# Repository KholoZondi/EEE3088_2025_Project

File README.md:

The repo stores all the shared work between EEE3088F Group 58 members Kholofelo Zondi and Max Mendelow for the Micro-mouse project project 2025. 

This includes the datasheets for certain ICs, past designs, general personal notes, downloaded schematics and the final design with Gerber and production files.

For the final design of the power subsystem, please navigate to "Micro_mouse_circuit/Micro_mouse_final" and consider the contents of the folder "Micro_mouse final" 
as the final design as of April 9th 2025. 

Full names and student numbers
Kholofelo Zondi ZNDKHO003
Max Mendelow MNDMAX003

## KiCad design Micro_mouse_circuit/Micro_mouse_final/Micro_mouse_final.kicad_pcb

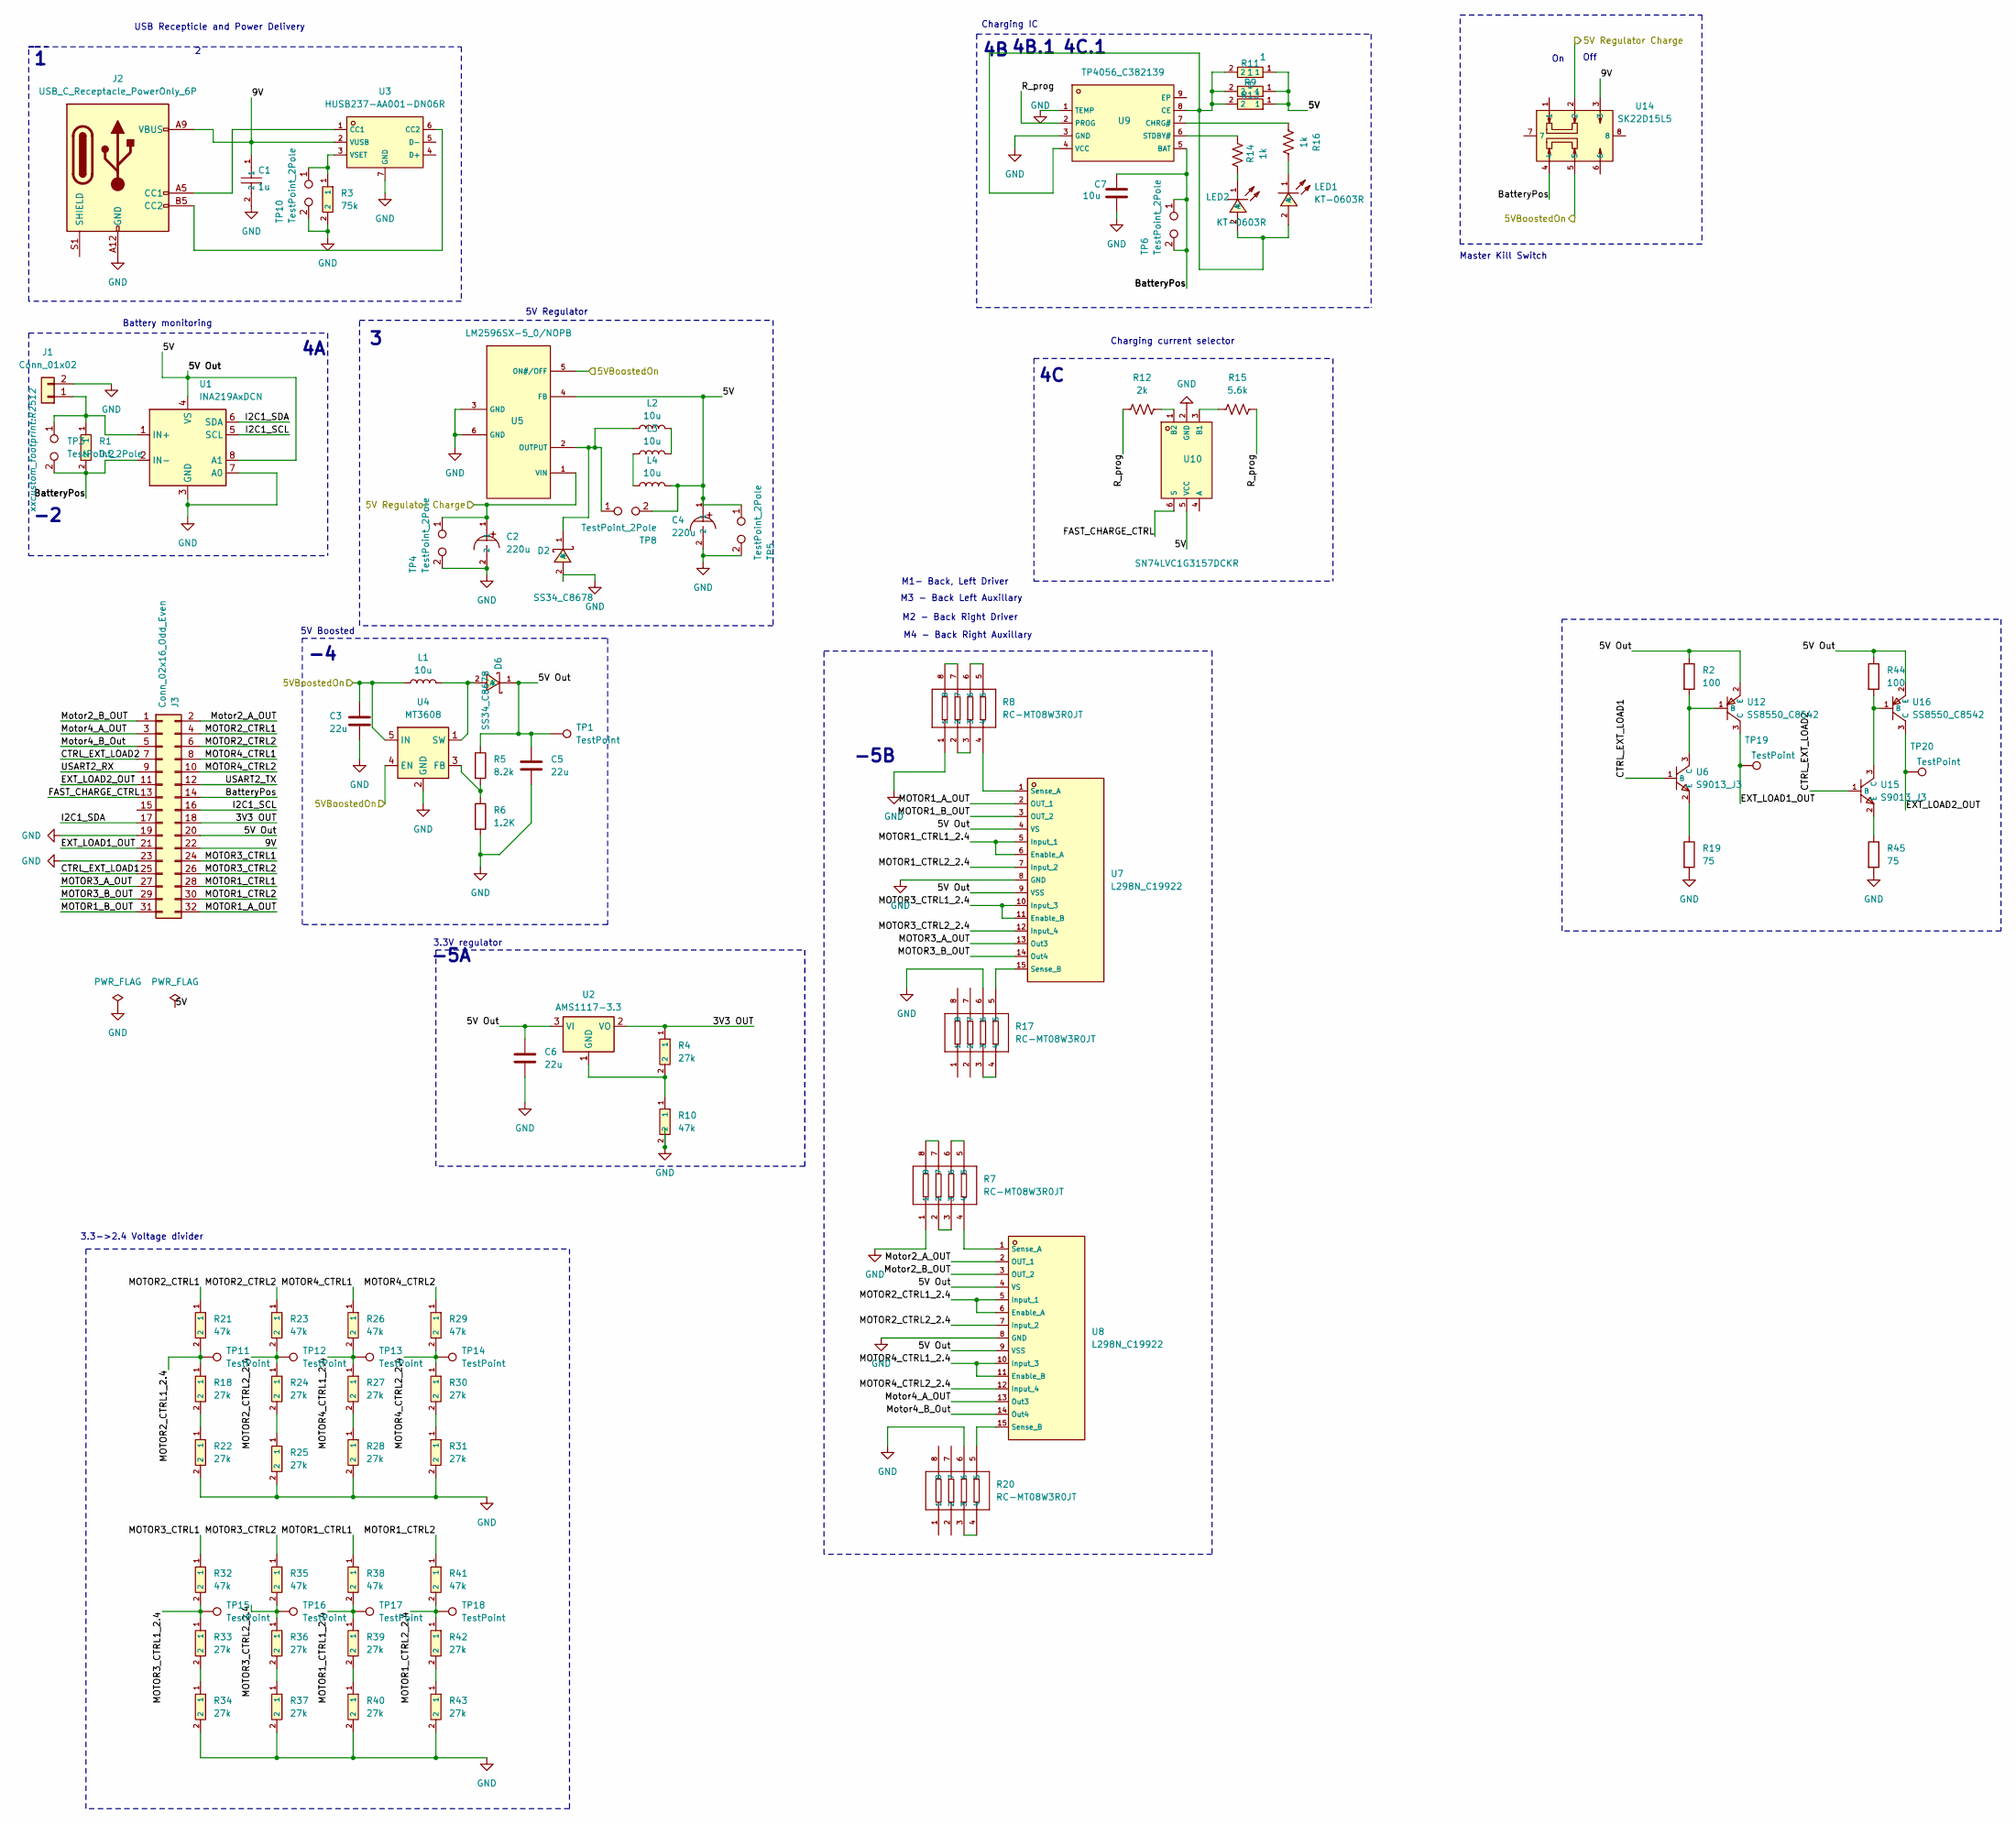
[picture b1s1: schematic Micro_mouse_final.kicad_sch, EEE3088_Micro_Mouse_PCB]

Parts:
C1: 1u; C1206; LCSC C1848
C2, C4: 220u; CAP-SMD_BD6.3-L6.6-W6.6-FD; LCSC C2833309
C3, C5, C6: 22u; C1206
C7: 10u; CAP-SMD_L3.2-W1.6-RD-C7171; LCSC C7171
D2, D6: SS34_C8678; SMA_L4.3-W2.6-LS5.2-RD; LCSC C8678
J1: Conn_01x02; JST_PH_S2B-PH-K_1x02_P2.00mm_Horizontal
J2: USB_C_Receptacle_PowerOnly_6P; TYPE-C-SMD_TYPE-C-6P; LCSC C5187463
J3: Conn_02x16_Odd_Even; PinHeader_2x16_P2.54mm_Vertical
L1, L2, L3, L4: 10u; L0805; LCSC C1046
LED1: KT-0603R; R0603; LCSC C2286
LED2: KT-0603R; R0603; LCSC C2290
R1: 0.2; R2512; LCSC C459674
R2, R44: 100; R0805; LCSC C17408
R3: 75k; R0603; LCSC C23242
R4, R18, R22, R24, R25, R27, R28, R30, R31, R33, R34, R36, R37, R39, R40, R42, R43: 27k; R0805; LCSC C17593
R5: 8.2k; R0805; LCSC C17828
R6: 1.2K; R1206; LCSC C17379
R7, R8, R17, R20: RC-MT08W3R0JT; RES-ARRAY-SMD_0402-8P-L2.0-W1.0-BL; LCSC C2002
R9, R11, R13: 1; R1206; LCSC C17928
R10, R21, R23, R26, R29, R32, R35, R38, R41: 47k; R0805; LCSC C17713
R12: 2k; R1206; LCSC C17944
R14, R16: 1k; R1206; LCSC C4410
R15: 5.6k; R0805; LCSC C4382
R19, R45: 75; R0603; LCSC C4275
TP1, TP11, TP12, TP13, TP14, TP15, TP16, TP17, TP18, TP19, TP20: TestPoint; TestPoint_Pad_2.5x2.5mm
TP3, TP4, TP5, TP6, TP8, TP10: TestPoint_2Pole; TestPoint_2Pads_Pitch2.54mm_Drill0.8mm
U1: INA219AxDCN; SOT-23-8; LCSC C87469
U2: AMS1117-3.3; SOT-223-3_L6.5-W3.4-P2.30-LS7.0-BR; LCSC C6186
U3: HUSB237-AA001-DN06R; TDFN-6_L2.0-W2.0-P0.65-TL-EP; LCSC C22373734
U4: MT3608; SOT-23-6_L2.9-W1.6-P0.95-LS2.8-BL; LCSC C84817
U5: LM2596SX-5_0/NOPB; TO-263-5_L10.2-W8.9-P1.70-TL; LCSC C10002
U6, U15: S9013_J3; SOT-23; LCSC C6749
U7, U8: L298N_C19922; MULTIWATT-15_L19.6-W5.0-P1.27-L; LCSC C19922
U9: TP4056_C382139; ESOP-8_L4.9-W3.9-P1.27-LS6.0-BL-EP; LCSC C382139
U10: SN74LVC1G3157DCKR; SC-70-6_L2.2-W1.3-P0.65-LS2.1-BR; LCSC C38663
U12, U16: SS8550_C8542; SOT-23; LCSC C8542
U14: SK22D15L5; SW-TH_XKB_SK22D15L7; LCSC C2884795

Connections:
/3V3 OUT: J3.18, R4.1, U2.2 (VO)
/5V: C4.1, C5.1, C6.1, D6.1 (K), J3.20, L4.2, R2.1, R5.1, R9.1, R11.1, R13.1, R44.1, TP1.1, TP5.1, TP8.2, U1.4 (VS), U1.8 (A1), U2.3 (VI), U5.4 (FB), U7.4 (VS), U7.9 (VSS), U8.4 (VS), U8.9 (VSS), U10.5 (VCC), U12.2 (E), U16.2 (E)
/5V Regulator Charge: C2.1, TP4.1, U5.1 (VIN), U14.2
/5VBoostedOn: C3.1, L1.1, U4.4 (EN), U4.5 (IN), U5.5 (ON#/OFF), U14.5
/9V: C1.1, J2.A9 (VBUS), J2.B9 (VBUS), J3.22, U3.2 (VUSB), U14.3
/BatteryPos: C7.1, J3.14, R1.2, TP3.2, TP6.1, TP6.2, U1.2 (IN-), U9.5 (BAT), U14.4
/CTRL_EXT_LOAD1: J3.25, U6.1 (B)
/CTRL_EXT_LOAD2: J3.7, U15.1 (B)
/EXT_LOAD1_OUT: J3.21, TP19.1, U12.3 (C)
/EXT_LOAD2_OUT: J3.11, TP20.1, U16.3 (C)
/FAST_CHARGE_CTRL: J3.13, U10.6 (S)
/I2C1_SCL: J3.16, U1.5 (SCL)
/I2C1_SDA: J3.17, U1.6 (SDA)
/MOTOR1_A_OUT: J3.32, U7.2 (OUT_1)
/MOTOR1_B_OUT: J3.31, U7.3 (OUT_2)
/MOTOR1_CTRL1: J3.28, R38.1
/MOTOR1_CTRL1_2.4: R38.2, R39.1, TP17.1, U7.5 (Input_1), U7.6 (Enable_A)
/MOTOR1_CTRL2: J3.30, R41.1
/MOTOR1_CTRL2_2.4: R41.2, R42.1, TP18.1, U7.7 (Input_2)
/MOTOR2_CTRL1: J3.4, R21.1
/MOTOR2_CTRL1_2.4: R18.1, R21.2, TP11.1, U8.5 (Input_1), U8.6 (Enable_A)
/MOTOR2_CTRL2: J3.6, R23.1
/MOTOR2_CTRL2_2.4: R23.2, R24.1, TP12.1, U8.7 (Input_2)
/MOTOR3_A_OUT: J3.27, U7.13 (Out3)
/MOTOR3_B_OUT: J3.29, U7.14 (Out4)
/MOTOR3_CTRL1: J3.24, R32.1
/MOTOR3_CTRL1_2.4: R32.2, R33.1, TP15.1, U7.10 (Input_3), U7.11 (Enable_B)
/MOTOR3_CTRL2: J3.26, R35.1
/MOTOR3_CTRL2_2.4: R35.2, R36.1, TP16.1, U7.12 (Input_4)
/MOTOR4_CTRL1: J3.8, R26.1
/MOTOR4_CTRL1_2.4: R26.2, R27.1, TP13.1, U8.10 (Input_3), U8.11 (Enable_B)
/MOTOR4_CTRL2: J3.10, R29.1
/MOTOR4_CTRL2_2.4: R29.2, R30.1, TP14.1, U8.12 (Input_4)
/Motor2_A_OUT: J3.2, U8.2 (OUT_1)
/Motor2_B_OUT: J3.1, U8.3 (OUT_2)
/Motor4_A_OUT: J3.3, U8.13 (Out3)
/Motor4_B_Out: J3.5, U8.14 (Out4)
/R_prog: R12.1, R15.1, U9.2 (PROG)
/USART2_RX: J3.9
/USART2_TX: J3.12
GND: C1.2, C2.2, C3.2, C4.2, C5.2, C6.2, C7.2, D2.2 (A), J1.2, J2.A12 (GND), J2.B12 (GND), J3.19, J3.23, R3.2, R6.2, R7.1, R8.1, R10.2, R17.6, R19.2, R20.6, R22.2, R25.2, R28.2, R31.2, R34.2, R37.2, R40.2, R43.2, R45.2, TP4.2, TP5.2, TP10.2, U1.3 (GND), U1.7 (A0), U3.7 (GND), U4.2 (GND), U5.3 (GND), U5.6 (GND), U7.8 (GND), U8.8 (GND), U9.1 (TEMP), U9.3 (GND), U10.2 (GND)
unnamed: D2.1 (K), L2.1, TP8.1, U5.2 (OUTPUT)
unnamed: D6.2 (A), L1.2, U4.1 (SW)
unnamed: J1.1, R1.1, TP3.1, U1.1 (IN+)
unnamed: J2.A5 (CC1), U3.1 (CC1)
unnamed: J2.B5 (CC2), U3.6 (CC2)
unnamed: L2.2, L3.2
unnamed: L3.1, L4.1
unnamed: LED1.2 (A), LED2.2 (A), R9.2, R11.2, R13.2, U9.4 (VCC), U9.8 (CE)
unnamed: LED1.1 (K), R16.1
unnamed: LED2.1 (K), R14.2
unnamed: R7.2, R7.3
unnamed: R7.5, R7.6
unnamed: R7.7, R7.8
unnamed: R8.2, R8.3
unnamed: R8.5, R8.6
unnamed: R8.7, R8.8
unnamed: R17.3, R17.4
unnamed: R18.2, R22.1
unnamed: R20.3, R20.4
unnamed: R24.2, R25.1
unnamed: R27.2, R28.1
unnamed: R30.2, R31.1
unnamed: R33.2, R34.1
unnamed: R36.2, R37.1
unnamed: R39.2, R40.1
unnamed: R42.2, R43.1
unnamed: R4.2, R10.1, U2.1 (GND)
unnamed: R3.1, TP10.1, U3.3 (VSET)
unnamed: R5.2, R6.1, U4.3 (FB)
unnamed: R19.1, U6.2 (E)
unnamed: R8.4, U7.1 (Sense_A)
unnamed: R17.5, U7.15 (Sense_B)
unnamed: R7.4, U8.1 (Sense_A)
unnamed: R20.5, U8.15 (Sense_B)
unnamed: R16.2, U9.7 (CHRG#)
unnamed: R14.1, U9.6 (STDBY#)
unnamed: R15.2, U10.3 (B1)
unnamed: R12.2, U10.1 (B2)
unnamed: R2.2, U6.3 (C), U12.1 (B)
unnamed: R44.2, U15.3 (C), U16.1 (B)
unnamed: R45.1, U15.2 (E)

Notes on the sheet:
5V Boosted
Charging current selector
4C.1
Battery monitoring
4B.1
M3 - Back Left Auxillary
Master Kill Switch
5V Regulator
Charging IC
-5A
Off
3.3->2.4 Voltage divider
-5B
M4 - Back Right Auxillary
M2 - Back Right Driver
3.3V regulator
USB Recepticle and Power Delivery
M1- Back, Left Driver

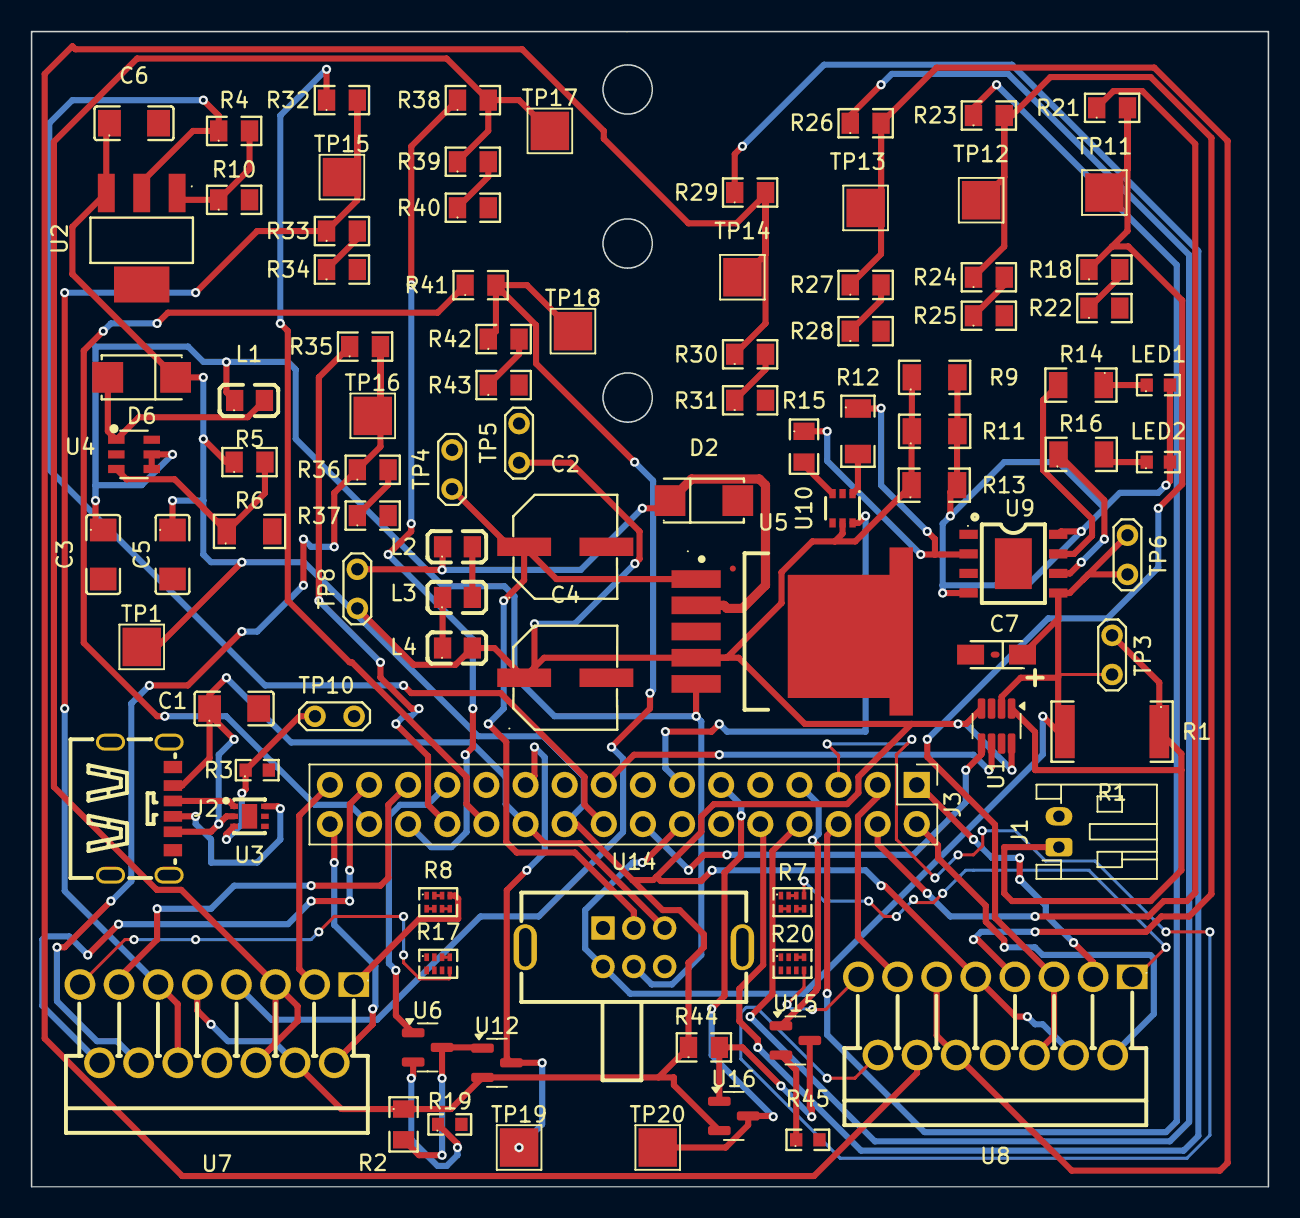
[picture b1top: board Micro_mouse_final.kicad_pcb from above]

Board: 2 copper layers, 80.3 x 75.0 mm, 94 parts (0 on the bottom side), 80 nets.

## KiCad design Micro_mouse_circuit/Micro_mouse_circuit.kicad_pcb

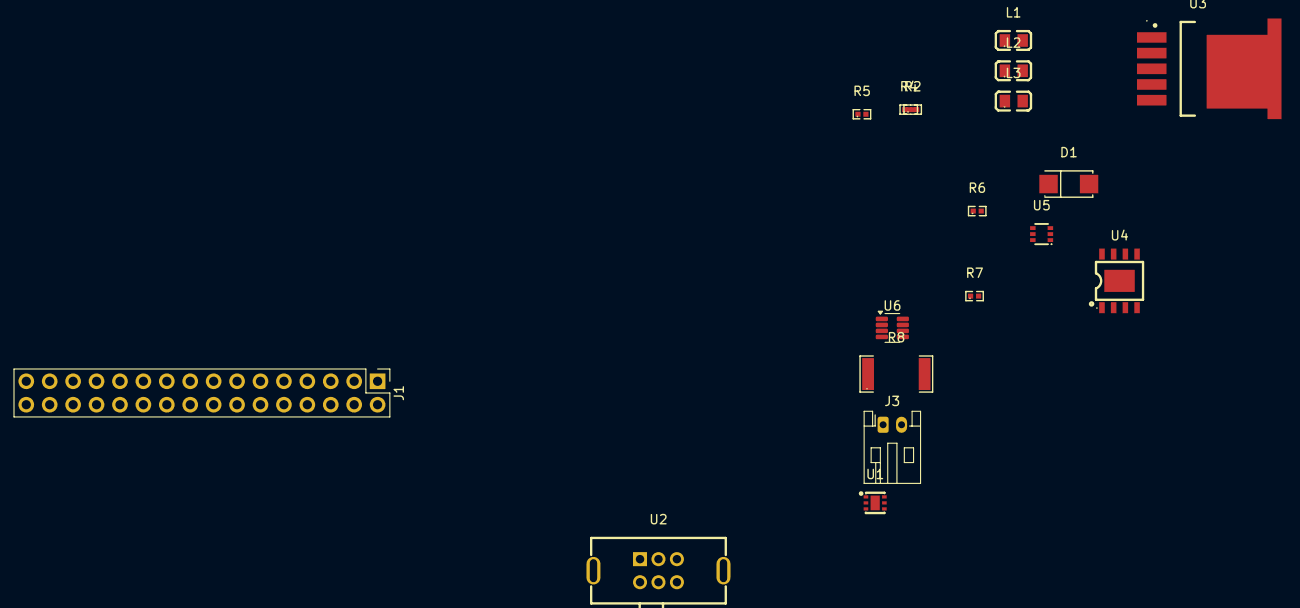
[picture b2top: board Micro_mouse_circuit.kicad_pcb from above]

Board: 2 copper layers, 18 parts (0 on the bottom side), 18 nets, no tracks yet.

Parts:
D1: SS34_C8678; SMA_L4.3-W2.6-LS5.2-RD
J1: Conn_02x16_Odd_Even; PinHeader_2x16_P2.54mm_Vertical
J3: Conn_01x02; JST_PH_S2B-PH-K_1x02_P2.00mm_Horizontal
L1, L2, L3: 10uH; L0805
R2, R6: 2k; R0402
R4, R5: 1k; R0402
R7: 6k; R0402
R8: 0.2A; R2512
U1: HUSB237-AA001-DN06R; TDFN-6_L2.0-W2.0-P0.65-TL-EP
U2: SK22D15L5; SW-TH_XKB_SK22D15L7
U3: LM2596SX-5_0/NOPB; TO-263-5_L10.2-W8.9-P1.70-TL
U4: TP4056_C382139; ESOP-8_L4.9-W3.9-P1.27-LS6.0-BL-EP
U5: SN74LVC1G3157DCKR; SC-70-6_L2.2-W1.3-P0.65-LS2.1-BR
U6: INA219AxDCN; SOT-23-8

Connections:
5V: L1.2, R2.1, U3.4 (FB), U4.8 (CE), U6.4 (VS), U6.8 (A1)
9V: J1.22, U1.2 (VUSB), U2.2, U3.1 (VIN)
/FAST_CHARGE_CTRL: J1.13, U5.6 (S)
/I2C1_SCL: J1.16, U6.5 (SCL)
/I2C1_SDA: J1.17, U6.6 (SDA)
/R_prog: R6.1, R7.1, U4.2 (PROG)
Battery: J1.14, U4.5 (BAT)
GND: D1.2 (A), J1.19, J1.23, J3.2, U1.7 (GND), U3.3 (GND), U3.5 (ON#/OFF), U3.6 (GND), U4.1 (TEMP), U4.3 (GND), U5.2 (GND), U6.3 (GND), U6.7 (A0)
unnamed: D1.1 (K), L2.1, U3.2 (OUTPUT)
unnamed: J3.1, R8.1
unnamed: L1.1, L3.1
unnamed: L2.2, L3.2
unnamed: R5.2, U4.7 (CHRG#)
unnamed: R4.1, U4.6 (STDBY#)
unnamed: R2.2, U4.4 (VCC)
unnamed: R7.2, U5.3 (B1)
unnamed: R6.2, U5.1 (B2)
unnamed: R8.2, U6.1 (IN+)

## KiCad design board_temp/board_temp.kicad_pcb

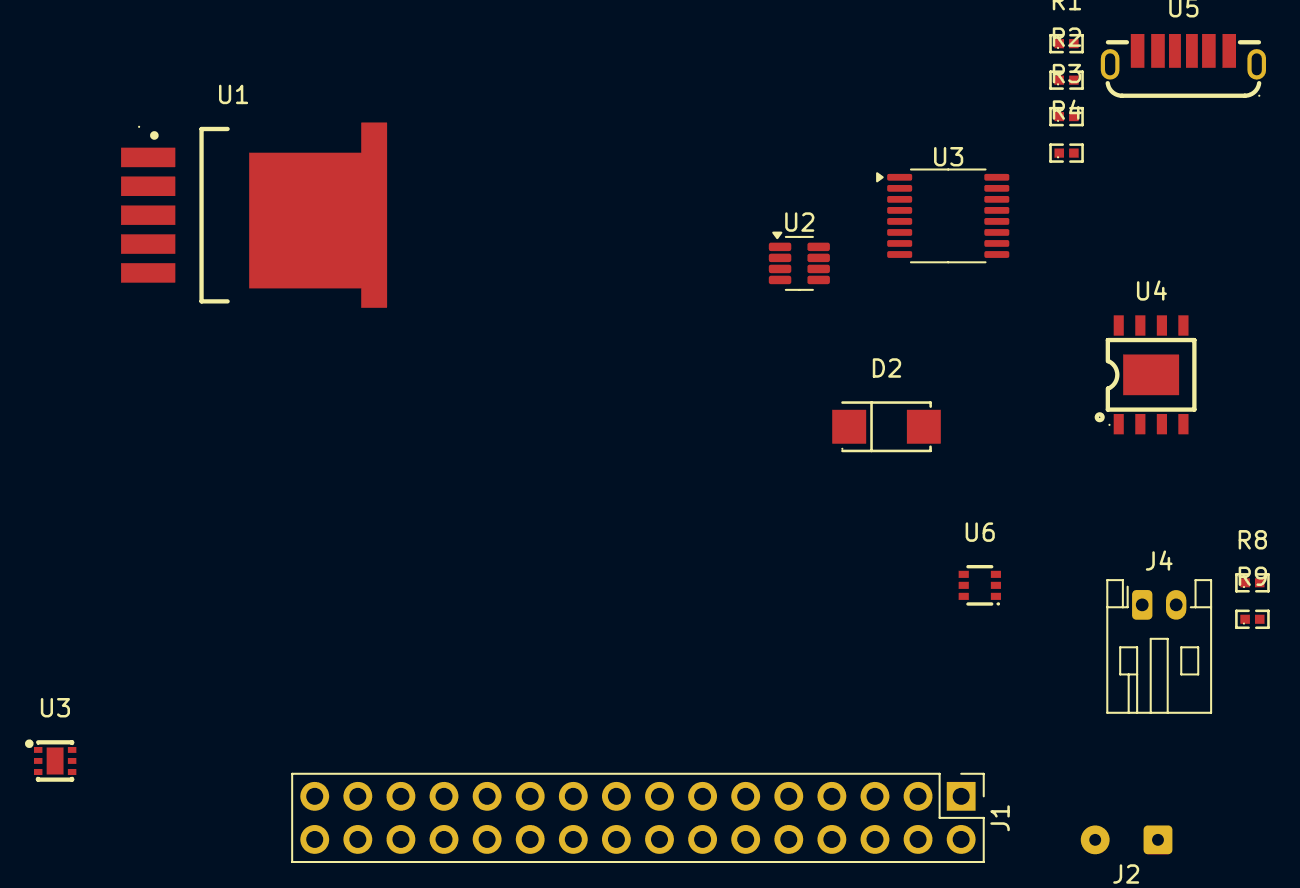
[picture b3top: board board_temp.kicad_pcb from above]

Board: 2 copper layers, 17 parts (0 on the bottom side), 13 nets, no tracks yet.

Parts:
D2: SS34_C8678; SMA_L4.3-W2.6-LS5.2-RD
J1: Conn_02x16_Odd_Even; PinHeader_2x16_P2.54mm_Vertical
J2: Battery input; SolderWire-0.127sqmm_1x02_P3.7mm_D0.48mm_OD1mm
J4: Conn_01x02; JST_PH_S2B-PH-K_1x02_P2.00mm_Horizontal
R1, R2, R8: 2k; R0402
R3, R4: 1k; R0402
R9: 6k; R0402
U1: LM2596SX-5_0/NOPB; TO-263-5_L10.2-W8.9-P1.70-TL
U2: INA219AxDCN; SOT-23-8
U3: HUSB237-AA001-DN06R; TDFN-6_L2.0-W2.0-P0.65-TL-EP
U3#2: IP2721; TSSOP-16_4.4x5mm_P0.65mm
U4: TP4056_C382139; ESOP-8_L4.9-W3.9-P1.27-LS6.0-BL-EP
U5: TYPE-C_6P_LTH6_5; USB-TYPE-C-SMD_TYPE-C-6P-LTH6.5
U6: SN74LVC1G3157DCKR; SC-70-6_L2.2-W1.3-P0.65-LS2.1-BR

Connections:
9V: J1.22, U1.1 (VIN), U3.2 (VUSB)
/I2C1_SCL: J1.16, U2.5 (SCL), U2.7 (A0)
/I2C1_SDA: J1.17, U2.6 (SDA), U2.8 (A1)
/R_prog: R8.1, R9.1, U4.2 (PROG)
/fast_charge: J1.13, U6.6 (S)
Buck_22: R2.1, U1.4 (FB), U4.8 (CE)
GND: D2.2 (A), J2.2, R1.1, U1.3 (GND), U1.5 (ON#/OFF), U1.6 (GND), U2.3 (GND), U3.7 (GND), U4.1 (TEMP), U4.3 (GND), U6.2 (GND)
unnamed: D2.1 (K), U1.2 (OUTPUT)
unnamed: R4.2, U4.7 (CHRG#)
unnamed: R3.1, U4.6 (STDBY#)
unnamed: R2.2, U4.4 (VCC)
unnamed: R9.2, U6.3 (B1)
unnamed: R8.2, U6.1 (B2)

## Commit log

2025-03-21 push
2025-03-25 changed charging config
2025-03-26 reorganized some files
2025-03-26 added USB PD
2025-03-26 began schematic rev 3.0
2025-03-26 adding footprint libraries
2025-03-27 assigned additional footprints
2025-03-28 4AM version of this circuit
2025-03-28 Board System 5
    -Includes block desegnations
2025-04-04 02/28 submission
2025-04-07 common share
2025-04-07 push - kt
2025-04-07 Max Half - PCB Board V6
    -Version before 2.4V regulation of motor control
    -Version before master kill switch
2025-04-09 FInal Additions to Schematic
    -Added Kill Switch
    -Moderated 3.3 Motor Control to 2.4 V
2025-04-09 push to Max - switch config finalized
2025-04-09 as last commit before
2025-04-09 common share update
